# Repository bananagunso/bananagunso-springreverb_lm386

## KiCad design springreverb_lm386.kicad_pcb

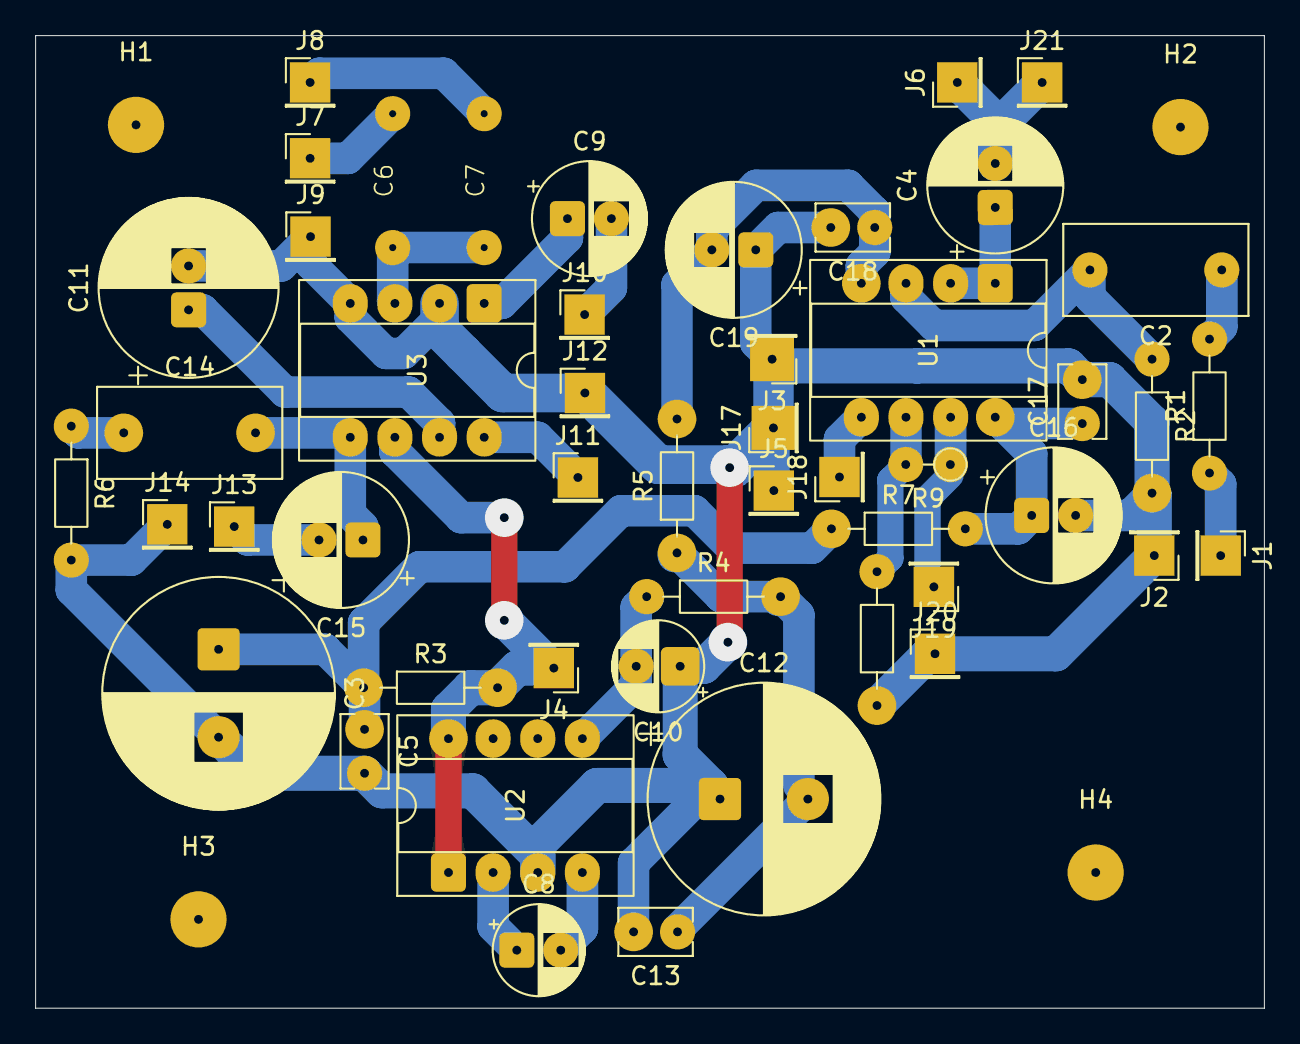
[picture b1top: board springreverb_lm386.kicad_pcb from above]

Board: 2 copper layers, 69.9 x 55.3 mm, 53 parts (0 on the bottom side), 27 nets.

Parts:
C2: 0.1u; C_Rect_L10.3mm_W5.0mm_P7.50mm_MKS4
C3, C12: 1000u; CP_Radial_D13.0mm_P5.00mm
C4, C15, C16, C19: 100u; CP_Radial_D7.5mm_P2.50mm
C5, C13, C17, C18: 0.1u; C_Rect_L4.0mm_W2.5mm_P2.50mm
C6: 0.1u; 10.5_5.0_p7.5
C7: 0.22u; 10.5_5.0_p7.5
C8, C10: 10u; CP_Radial_D5.0mm_P2.50mm
C9: 10u; CP_Radial_D6.3mm_P2.50mm
C11: 100u; CP_Radial_D10.0mm_P2.50mm
C14: 0.047u; C_Rect_L10.3mm_W5.0mm_P7.50mm_MKS4
H1, H2, H3, H4: MountingHole; MountingHole_3.2mm_M3
J1: IN; PinHeader_1x01_P2.54mm_Vertical
J2: INGND; PinHeader_1x01_P2.54mm_Vertical
J3: GND; PinHeader_1x01_P2.54mm_Vertical
J4: Vin; PinHeader_1x01_P2.54mm_Vertical
J5: LEDGND; PinHeader_1x01_P2.54mm_Vertical
J6: VR1_3; PinHeader_1x01_P2.54mm_Vertical
J7: toC6; PinHeader_1x01_P2.54mm_Vertical
J8: toC7; PinHeader_1x01_P2.54mm_Vertical
J9: FromC; PinHeader_1x01_P2.54mm_Vertical
J10, J19: VR2_3; PinHeader_1x01_P2.54mm_Vertical
J11: VR_2_2; PinHeader_1x01_P2.54mm_Vertical
J12: VR_2GND; PinHeader_1x01_P2.54mm_Vertical
J13: To; PinHeader_1x01_P2.54mm_Vertical
J14: FromSW; PinHeader_1x01_P2.54mm_Vertical
J17: FromGND; PinHeader_1x01_P2.54mm_Vertical
J18: From; PinHeader_1x01_P2.54mm_Vertical
J20: VR2_3GND; PinHeader_1x01_P2.54mm_Vertical
J21: VR3_1; PinHeader_1x01_P2.54mm_Vertical
R1: 10k; R_Axial_DIN0204_L3.6mm_D1.6mm_P7.62mm_Horizontal
R2: 1M; R_Axial_DIN0204_L3.6mm_D1.6mm_P7.62mm_Horizontal
R3, R4, R6: 10; R_Axial_DIN0204_L3.6mm_D1.6mm_P7.62mm_Horizontal
R5, R7: 470; R_Axial_DIN0204_L3.6mm_D1.6mm_P7.62mm_Horizontal
R8: 2.2k; R_Axial_DIN0204_L3.6mm_D1.6mm_P7.62mm_Horizontal
R9: 220k; R_Axial_DIN0204_L3.6mm_D1.6mm_P2.54mm_Vertical
U1: TL072; CERDIP-8_W7.62mm_SideBrazed_Socket
U2: TC1044S; CERDIP-8_W7.62mm_SideBrazed_Socket
U3: LM386; CERDIP-8_W7.62mm_SideBrazed_Socket

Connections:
GND: C3.2, C5.2, C10.1, C11.2, C12.1, C13.2, C16.2, C17.2, C18.2, C19.1, J2.1 (Pin_1_1), J3.1 (Pin_1_1), J5.1 (Pin_1_1), J9.1 (Pin_1_1), J12.1 (Pin_1_1), J14.1 (Pin_1_1), J17.1 (Pin_1_1), J20.1 (Pin_1_1), R2.2, R6.2, R8.2, U2.3 (GND), U3.2 (-), U3.4 (GND)
unnamed: C2.1, R1.2
unnamed: C3.1, C5.1, R3.1, R7.1
unnamed: C9.1, U3.1 (GAIN)
unnamed: C12.2, C13.1, R4.2, R5.1
unnamed: C14.1, R6.1
unnamed: C14.2, C15.1, U3.5
unnamed: J1.1 (Pin_1_1), R1.1
unnamed: J4.1 (Pin_1_1), R3.2, U2.1 (BOOST), U2.8 (V+), U3.6 (V+)
unnamed: C6.2, J7.1 (Pin_1_1)
unnamed: C7.2, J8.1 (Pin_1_1)
unnamed: C9.2, J10.1 (Pin_1_1)
unnamed: J11.1 (Pin_1_1), U3.8 (GAIN)
unnamed: C15.2, J13.1 (Pin_1_1)
unnamed: J18.1 (Pin_1_1), U1.5 (+)
unnamed: J19.1 (Pin_1_1), R9.1, U1.7
unnamed: C4.2, J6.1 (Pin_1_1), J21.1 (Pin_1_1)
unnamed: C2.2, R2.1, U1.3 (+)
unnamed: C4.1, U1.1, U1.2 (-)
unnamed: R8.1, R9.2, U1.6 (-)
unnamed: C16.1, C17.1, R7.2, U1.8 (V+)
unnamed: C18.1, C19.2, R5.2, U1.4 (V-)
unnamed: C8.1, U2.2 (CAP+)
unnamed: C8.2, U2.4 (CAP-)
unnamed: C10.2, R4.1, U2.5 (VOUT)
unnamed: C6.1, C7.1, U3.3 (+)
unnamed: C11.1, U3.7 (BYPASS)

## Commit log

2026-04-21 init
2026-04-21 一旦回路完成
2026-04-21 少し修正
